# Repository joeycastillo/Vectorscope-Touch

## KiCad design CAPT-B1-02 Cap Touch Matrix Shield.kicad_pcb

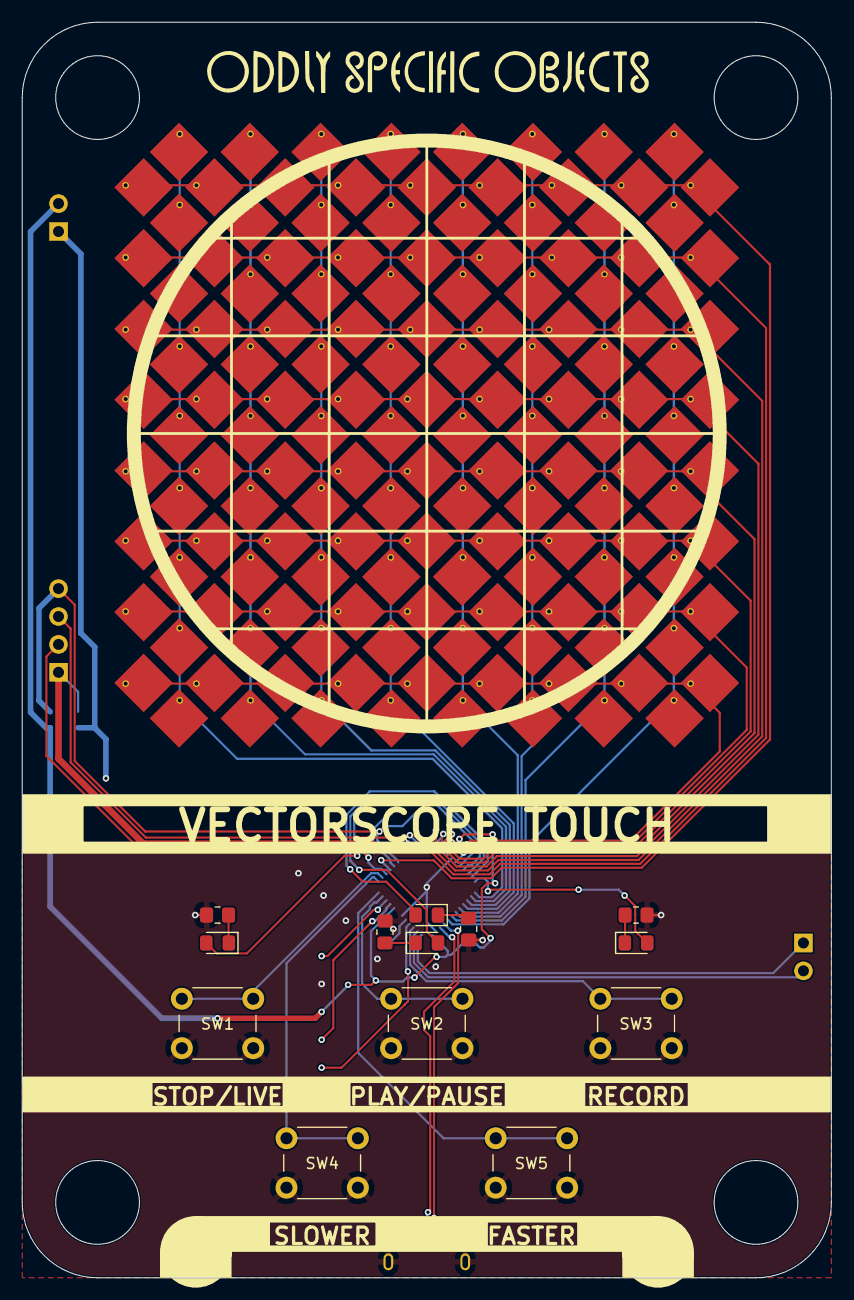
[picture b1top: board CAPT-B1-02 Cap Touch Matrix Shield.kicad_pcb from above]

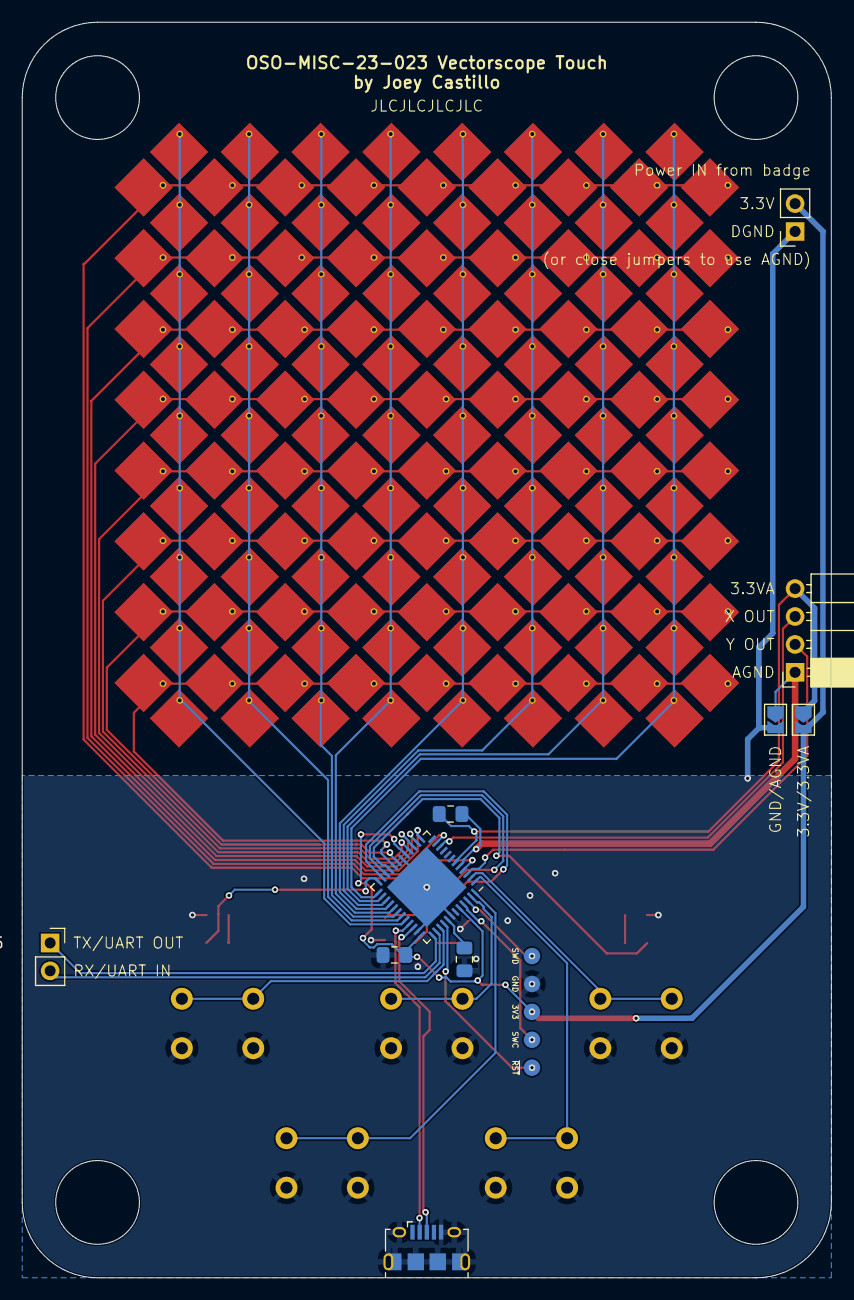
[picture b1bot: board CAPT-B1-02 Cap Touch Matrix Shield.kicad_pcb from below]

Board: 2 copper layers, 73.7 x 114.3 mm, 25 parts (11 on the bottom side), 43 nets.

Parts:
C1, C2, C3: C; C_0805_2012Metric_Pad1.18x1.45mm_HandSolder
CT2: MATRIX_ACTIVE_8X8SEG_6MM
D1, D2, D3, D4: LED; LED_0805_2012Metric_Pad1.15x1.40mm_HandSolder
J1: Conn_01x04_Socket; PinSocket_1x04_P2.54mm_Horizontal
J2, J5: Conn_01x02_Socket; PinSocket_1x02_P2.54mm_Vertical
J3: USB_B_Micro; USB_Micro-B_Amphenol_10118194_Horizontal
J4: OSO_SWD; OSO_SWD_Linear
JP1, JP2: Jumper_2_Open; SolderJumper-2_P1.3mm_Open_TrianglePad1.0x1.5mm
R1, R2, R3, R4: R; R_0805_2012Metric_Pad1.20x1.40mm_HandSolder
SW1, SW2, SW3, SW4, SW5: SW_Push; SW_PUSH_6mm
U1: ATSAML21G18B-MUT; QFN-48-1EP_7x7mm_P0.5mm_EP5.15x5.15mm

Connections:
+3.3V: C1.2, J2.2, J4.3 (VCC), JP1.2 (B), U1.17 (VDDIO), U1.36 (VDDIO), U1.44 (VDDIN)
+3.3VA: C2.2, J1.4, JP1.1 (A), U1.6 (VDDANA)
/INT0: SW4.1, U1.1 (PA00)
/INT1: SW1.1, U1.2 (PA01)
/INT2: SW2.1, U1.47 (PB02)
/INT3: SW5.1, U1.48 (PB03)
/INT15: SW3.1, U1.39 (PA27)
/LED0: D1.2 (A), U1.21 (PA12)
/LED1: D2.2 (A), U1.22 (PA13)
/LED2: D3.2 (A), U1.23 (PA14)
/LED3: D4.2 (A), U1.24 (PA15)
/RX: J5.2, U1.38 (PB23)
/SWCLK: J4.4 (SWCLK), U1.45 (PA30)
/SWDIO: J4.1 (SWDIO), U1.46 (PA31)
/TX: J5.1, U1.37 (PB22)
/USB+: J3.3 (D+), U1.34 (PA25)
/USB-: J3.2 (D-), U1.33 (PA24)
/VDDCORE: C3.2, U1.41 (VDDCORE)
/X0: CT2.X0Y0, CT2.X0Y1, CT2.X0Y2, CT2.X0Y3, CT2.X0Y4, CT2.X0Y5, CT2.X0Y6, CT2.X0Y7, CT2.X0Y8, U1.25 (PA16)
/X1: CT2.X1Y0, CT2.X1Y1, CT2.X1Y2, CT2.X1Y3, CT2.X1Y4, CT2.X1Y5, CT2.X1Y6, CT2.X1Y7, CT2.X1Y8, U1.26 (PA17)
/X2: CT2.X2Y0, CT2.X2Y1, CT2.X2Y2, CT2.X2Y3, CT2.X2Y4, CT2.X2Y5, CT2.X2Y6, CT2.X2Y7, CT2.X2Y8, U1.27 (PA18)
/X3: CT2.X3Y0, CT2.X3Y1, CT2.X3Y2, CT2.X3Y3, CT2.X3Y4, CT2.X3Y5, CT2.X3Y6, CT2.X3Y7, CT2.X3Y8, U1.28 (PA19)
/X4: CT2.X4Y0, CT2.X4Y1, CT2.X4Y2, CT2.X4Y3, CT2.X4Y4, CT2.X4Y5, CT2.X4Y6, CT2.X4Y7, CT2.X4Y8, U1.29 (PA20)
/X5: CT2.X5Y0, CT2.X5Y1, CT2.X5Y2, CT2.X5Y3, CT2.X5Y4, CT2.X5Y5, CT2.X5Y6, CT2.X5Y7, CT2.X5Y8, U1.30 (PA21)
/X6: CT2.X6Y0, CT2.X6Y1, CT2.X6Y2, CT2.X6Y3, CT2.X6Y4, CT2.X6Y5, CT2.X6Y6, CT2.X6Y7, CT2.X6Y8, U1.31 (PA22)
/X7: CT2.X7Y0, CT2.X7Y1, CT2.X7Y2, CT2.X7Y3, CT2.X7Y4, CT2.X7Y5, CT2.X7Y6, CT2.X7Y7, CT2.X7Y8, U1.32 (PA23)
/XOUT: J1.3, U1.10 (PA05)
/Y0: CT2.Y0X0, CT2.Y0X1, CT2.Y0X2, CT2.Y0X3, CT2.Y0X4, CT2.Y0X5, CT2.Y0X6, CT2.Y0X7, CT2.Y0X8, U1.4 (PA03)
/Y1: CT2.Y1X0, CT2.Y1X1, CT2.Y1X2, CT2.Y1X3, CT2.Y1X4, CT2.Y1X5, CT2.Y1X6, CT2.Y1X7, CT2.Y1X8, U1.11 (PA06)
/Y2: CT2.Y2X0, CT2.Y2X1, CT2.Y2X2, CT2.Y2X3, CT2.Y2X4, CT2.Y2X5, CT2.Y2X6, CT2.Y2X7, CT2.Y2X8, U1.13 (PA08)
/Y3: CT2.Y3X0, CT2.Y3X1, CT2.Y3X2, CT2.Y3X3, CT2.Y3X4, CT2.Y3X5, CT2.Y3X6, CT2.Y3X7, CT2.Y3X8, U1.14 (PA09)
/Y4: CT2.Y4X0, CT2.Y4X1, CT2.Y4X2, CT2.Y4X3, CT2.Y4X4, CT2.Y4X5, CT2.Y4X6, CT2.Y4X7, CT2.Y4X8, U1.15 (PA10)
/Y5: CT2.Y5X0, CT2.Y5X1, CT2.Y5X2, CT2.Y5X3, CT2.Y5X4, CT2.Y5X5, CT2.Y5X6, CT2.Y5X7, CT2.Y5X8, U1.16 (PA11)
/Y6: CT2.Y6X0, CT2.Y6X1, CT2.Y6X2, CT2.Y6X3, CT2.Y6X4, CT2.Y6X5, CT2.Y6X6, CT2.Y6X7, CT2.Y6X8, U1.19 (PB10)
/Y7: CT2.Y7X0, CT2.Y7X1, CT2.Y7X2, CT2.Y7X3, CT2.Y7X4, CT2.Y7X5, CT2.Y7X6, CT2.Y7X7, CT2.Y7X8, U1.20 (PB11)
/YOUT: J1.2, U1.3 (PA02)
/~RESET: J4.5 (~RESET), U1.40 (~RESET)
GND: C1.1, C3.1, J2.1, J3.5 (GND), J3.6 (Shield), J4.2 (GND), JP2.2 (B), R1.1, R2.1, R3.1, R4.1, SW1.2, SW2.2, SW3.2, SW4.2, SW5.2, U1.18 (GND), U1.35 (GND), U1.42 (GND), U1.49
GNDA: C2.1, J1.1, JP2.1 (A), U1.5 (GNDANA)
unnamed: D1.1 (K), R1.2
unnamed: D2.1 (K), R2.2
unnamed: D3.1 (K), R3.2
unnamed: D4.1 (K), R4.2
